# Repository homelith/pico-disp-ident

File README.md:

# pico-disp-ident

## これは何？

- RP2040 搭載ボードと PicoDVI (https://github.com/Wren6991/PicoDVI) を使って、DVI ディスプレイに番号入りのテストパターン表示をさせるツールです。
- PicoDVI の feat/x8scale ブランチ (https://github.com/homelith/PicoDVI/tree/feat/x8scale) 版を用いることで、80x60 画像を VGA 640x480 ディスプレイに引き延ばして表示します。

## ハードウェア構築

- 記載中

## ソフトウェアビルド

- 環境準備
  + Linux ベースの OS 各種上でコンパイル可能と想定 (x86_64 ネイティブの ubuntu 22.04 LTS と WSL2 上の ubuntu 22.04 LTS で試験済)
  + パッケージインストール : `sudo apt install git gcc make cmake gcc-arm-none-eabi libnewlib-arm-none-eabi build-essential golang`

- uf2 バイナリをコンパイルする手順
  + 下記手順でコンパイル後、`sw/build/app/pico-disp-ident.uf2` が得られます

```
$ git clone --recursive git@github.com:homelith/pico-disp-ident.git
$ cd pico-disp-ident/sw
$ make
```

## デバイスを動作させる手順

- Raspberry Pi Pico への uf2 ファイルダウンロード
  + BOOTSEL ボタンを押しながら Raspi Pico の電源を投入することで、USB ポートがマスストレージデバイスとして認識されます
  + `pico-disp-ident.uf2` ファイルを該当ストレージの直下に置くことで書き込みとセルフリセットが行われます

- ボタンを押下すると表示画像と対応する 7seg の表示番号が切り替わります

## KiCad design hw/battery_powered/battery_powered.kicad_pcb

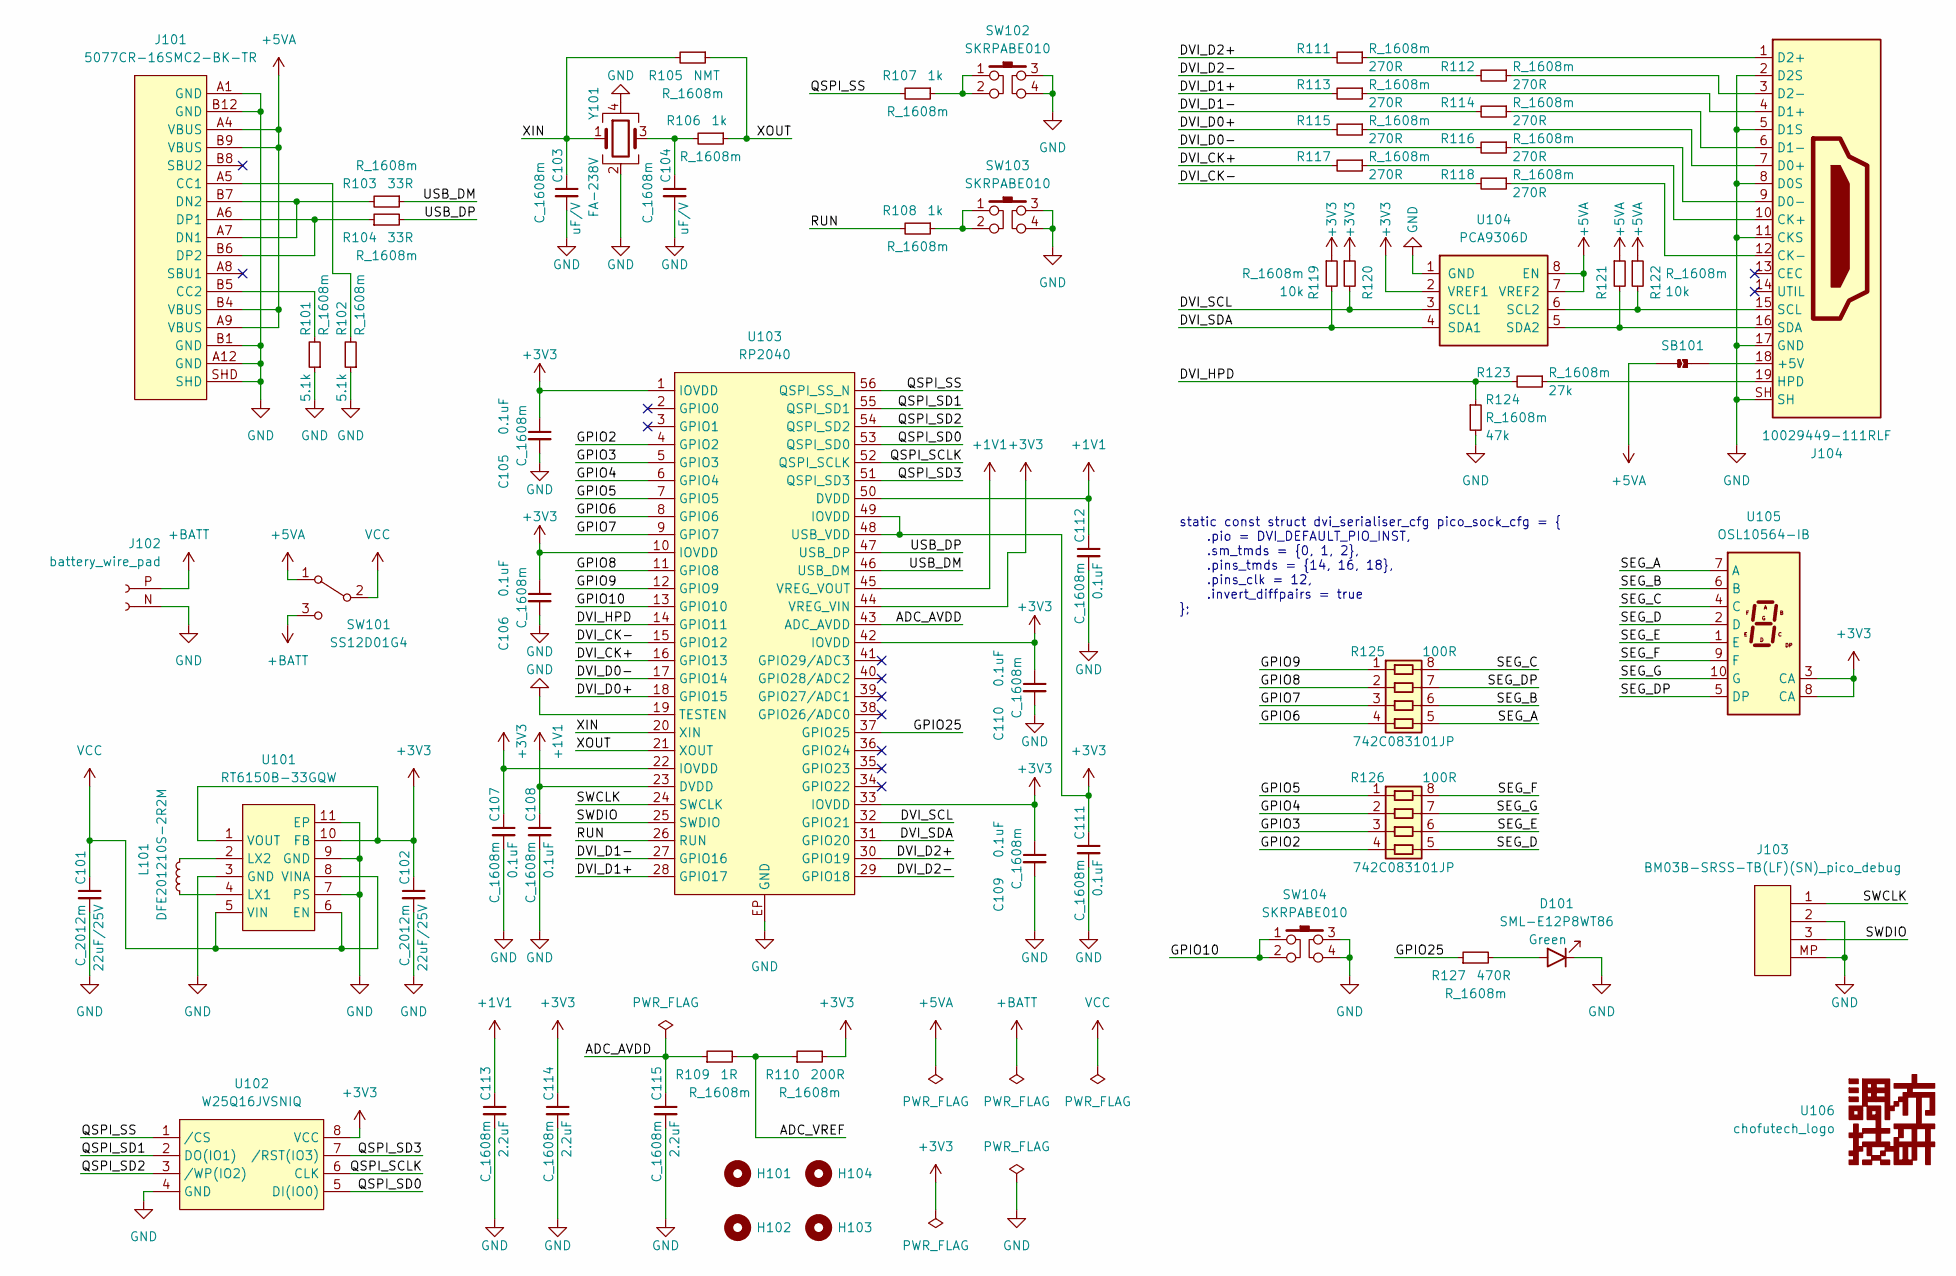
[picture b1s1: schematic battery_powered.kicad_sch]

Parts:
C101, C102: C_2012m
C103, C104, C105, C106, C107, C108, C109, C110, C111, C112, C113, C114, C115: C_1608m
D101: SML-E12P8WT86
H101, H102, H103, H104: MountingHole_2.2mm_M2; MountingHole_3.2mm_M3
J101: 5077CR-16SMC2-BK-TR; 5077CR-16SMC2-BK-TR_hand
J102: battery_wire_pad
J103: BM03B-SRSS-TB(LF)(SN)_pico_debug; BM03B-SRSS-TB(LF)(SN)_hand
J104: 10029449-111RLF; 10029449-111RLF_hand
L101: DFE201210S-2R2M
R101, R102, R103, R104, R105, R106, R107, R108, R109, R110, R111, R112, R113, R114, R115, R116, R117, R118, R119, R120, R121, R122, R123, R124, R127: R_1608m
R125, R126: 742C083101JP
SB101: jumper_2pole_solder
SW101: SS12D01G4
SW102, SW103, SW104: SKRPABE010; SKRPABE010_hand
U101: RT6150B-33GQW
U102: W25Q16JVSNIQ
U103: RP2040
U104: PCA9306D
U105: OSL10564-IB
U106: chofutech_logo; chofutech_logo_6.6mm
Y101: FA-238V

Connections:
+1V1: C108.1, C112.1, C113.1, U103.23 (DVDD), U103.45 (VREG_VOUT), U103.50 (DVDD)
+3V3: C102.1, C105.1, C106.1, C107.1, C109.1, C110.1, C111.1, C114.1, R110.2, R119.1, R120.1, U101.1 (VOUT), U101.10 (FB), U102.8 (VCC), U103.1 (IOVDD), U103.10 (IOVDD), U103.22 (IOVDD), U103.33 (IOVDD), U103.42 (IOVDD), U103.44 (VREG_VIN), U103.48 (USB_VDD), U103.49 (IOVDD), U104.2 (VREF1), U105.3 (CA), U105.8 (CA)
+5VA: J101.A4 (VBUS), J101.A9 (VBUS), J101.B4 (VBUS), J101.B9 (VBUS), R121.1, R122.1, SB101.1 (A), SW101.1 (A), U104.7 (VREF2), U104.8 (EN)
+BATT: J102.P (Pin_1), SW101.3 (C)
/ADC_AVDD: C115.1, R109.1, U103.43 (ADC_AVDD)
/ADC_VREF: R109.2, R110.1
/DVI_CK+: R117.2, U103.16 (GPIO13)
/DVI_CK-: R118.2, U103.15 (GPIO12)
/DVI_D0+: R115.2, U103.18 (GPIO15)
/DVI_D0-: R116.2, U103.17 (GPIO14)
/DVI_D1+: R113.2, U103.28 (GPIO17)
/DVI_D1-: R114.2, U103.27 (GPIO16)
/DVI_D2+: R111.2, U103.30 (GPIO19)
/DVI_D2-: R112.2, U103.29 (GPIO18)
/DVI_HPD: R123.2, R124.1, U103.14 (GPIO11)
/DVI_SCL: R120.2, U103.32 (GPIO21), U104.3 (SCL1)
/DVI_SDA: R119.2, U103.31 (GPIO20), U104.4 (SDA1)
/GPIO2: R126.4, U103.4 (GPIO2)
/GPIO3: R126.3, U103.5 (GPIO3)
/GPIO4: R126.2, U103.6 (GPIO4)
/GPIO5: R126.1, U103.7 (GPIO5)
/GPIO6: R125.4, U103.8 (GPIO6)
/GPIO7: R125.3, U103.9 (GPIO7)
/GPIO8: R125.2, U103.11 (GPIO8)
/GPIO9: R125.1, U103.12 (GPIO9)
/GPIO10: SW104.1, SW104.2, U103.13 (GPIO10)
/GPIO25: R127.1, U103.37 (GPIO25)
/QSPI_SCLK: U102.6 (CLK), U103.52 (QSPI_SCLK)
/QSPI_SD0: U102.5 (DI(IO0)), U103.53 (QSPI_SD0)
/QSPI_SD1: U102.2 (DO(IO1)), U103.55 (QSPI_SD1)
/QSPI_SD2: U102.3 (/WP(IO2)), U103.54 (QSPI_SD2)
/QSPI_SD3: U102.7 (/RST(IO3)), U103.51 (QSPI_SD3)
/QSPI_SS: R107.2, U102.1 (/CS), U103.56 (QSPI_SS_N)
/RUN: R108.2, U103.26 (RUN)
/SEG_A: R125.5, U105.7 (A)
/SEG_B: R125.6, U105.6 (B)
/SEG_C: R125.8, U105.4 (C)
/SEG_D: R126.5, U105.2 (D)
/SEG_DP: R125.7, U105.5 (DP)
/SEG_E: R126.6, U105.1 (E)
/SEG_F: R126.8, U105.9 (F)
/SEG_G: R126.7, U105.10 (G)
/SWCLK: J103.1, U103.24 (SWCLK)
/SWDIO: J103.3, U103.25 (SWDIO)
/USB_DM: R103.1, U103.46 (USB_DM)
/USB_DP: R104.2, U103.47 (USB_DP)
/XIN: C103.1, R105.2, U103.20 (XIN), Y101.1
/XOUT: R105.1, R106.1, U103.21 (XOUT)
GND: C101.2, C102.2, C103.2, C104.2, C105.2, C106.2, C107.2, C108.2, C109.2, C110.2, C111.2, C112.2, C113.2, C114.2, C115.2, D101.1 (K), J101.A1 (GND), J101.A12 (GND), J101.B1 (GND), J101.B12 (GND), J101.SHD, J102.N (Pin_2), J103.2, J103.MP, J104.2 (D2S), J104.5 (D1S), J104.8 (D0S), J104.11 (CKS), J104.17 (GND), J104.SH, R101.1, R102.1, R124.2, SW102.3, SW102.4, SW103.3, SW103.4, SW104.3, SW104.4, U101.3 (GND), U101.7 (PS), U101.9 (GND), U101.11 (EP), U102.4 (GND), U103.19 (TESTEN), U103.EP (GND), U104.1 (GND), Y101.2, Y101.4
unnamed: C104.1, R106.2, Y101.3
unnamed: D101.2 (A), R127.2
unnamed: J101.A5 (CC1), R102.2
unnamed: J101.A6 (DP1), J101.B6 (DP2), R104.1
unnamed: J101.A7 (DN1), J101.B7 (DN2), R103.2
unnamed: J101.B5 (CC2), R101.2
unnamed: J104.1 (D2+), R111.1
unnamed: J104.3 (D2-), R112.1
unnamed: J104.4 (D1+), R113.1
unnamed: J104.6 (D1-), R114.1
unnamed: J104.7 (D0+), R115.1
unnamed: J104.9 (D0-), R116.1
unnamed: J104.10 (CK+), R117.1
unnamed: J104.12 (CK-), R118.1
unnamed: J104.15 (SCL), R122.2, U104.6 (SCL2)
unnamed: J104.16 (SDA), R121.2, U104.5 (SDA2)
unnamed: J104.18 (+5V), SB101.2 (B)
unnamed: J104.19 (HPD), R123.1
unnamed: L101.1, U101.2 (LX2)
unnamed: L101.2, U101.4 (LX1)
unnamed: R107.1, SW102.1, SW102.2
unnamed: R108.1, SW103.1, SW103.2
VCC: C101.1, SW101.2 (B), U101.5 (VIN), U101.6 (EN), U101.8 (VINA)

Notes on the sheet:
static const struct dvi_serialiser_cfg pico_sock_cfg = { .pio = DVI_DEFAULT_PIO_INST, .sm_tmds = {0, 1, 2}, .pins_tmds = {14, 16, 18}, .pins_clk = 12, .invert_diffpairs = true };

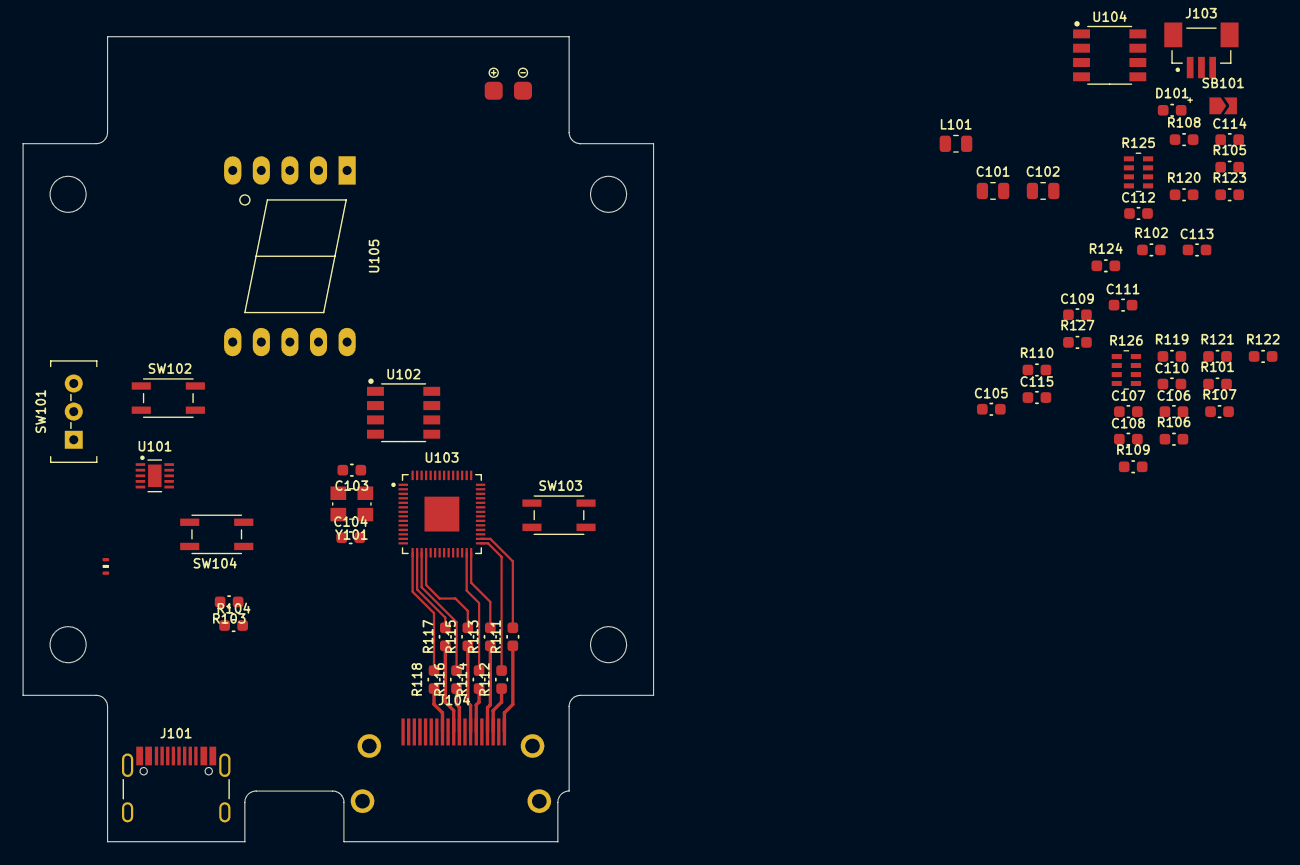
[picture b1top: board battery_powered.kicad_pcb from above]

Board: 4 copper layers, 56.0 x 71.5 mm, 64 parts (0 on the bottom side), 72 nets.

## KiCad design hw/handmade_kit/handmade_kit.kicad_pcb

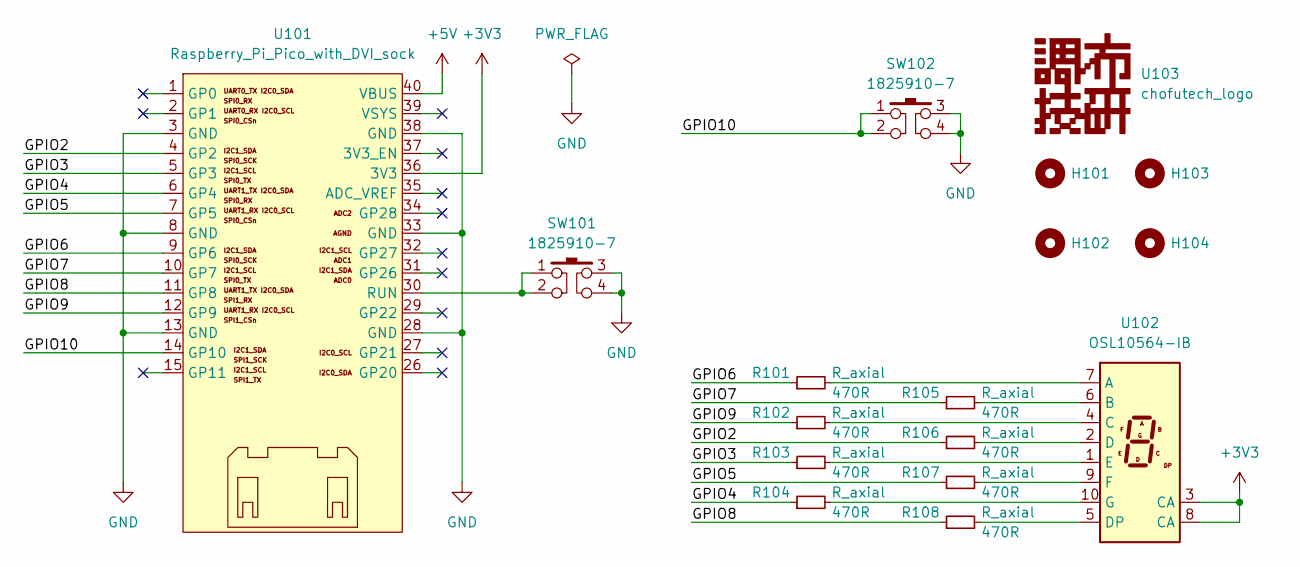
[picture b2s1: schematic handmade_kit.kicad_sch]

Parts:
H101, H102, H103, H104: MountingHole_2.2mm_M2
R101, R102, R103, R104, R105, R106, R107, R108: R_axial
SW101, SW102: 1825910-7
U101: Raspberry_Pi_Pico_with_DVI_sock
U102: OSL10564-IB
U103: chofutech_logo; chofutech_logo_6.6mm

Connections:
+3V3: U101.36 (3V3), U102.3 (CA), U102.8 (CA)
+5V: U101.40 (VBUS)
/GPIO2: R106.1, U101.4 (GP2)
/GPIO3: R103.1, U101.5 (GP3)
/GPIO4: R104.1, U101.6 (GP4)
/GPIO5: R107.1, U101.7 (GP5)
/GPIO6: R101.1, U101.9 (GP6)
/GPIO7: R105.1, U101.10 (GP7)
/GPIO8: R108.1, U101.11 (GP8)
/GPIO9: R102.1, U101.12 (GP9)
/GPIO10: SW102.1, SW102.2, U101.14 (GP10)
GND: SW101.3, SW101.4, SW102.3, SW102.4, U101.3 (GND), U101.8 (GND), U101.13 (GND), U101.28 (GND), U101.33 (GND), U101.38 (GND)
unnamed: R101.2, U102.7 (A)
unnamed: R102.2, U102.4 (C)
unnamed: R103.2, U102.1 (E)
unnamed: R104.2, U102.10 (G)
unnamed: R105.2, U102.6 (B)
unnamed: R106.2, U102.2 (D)
unnamed: R107.2, U102.9 (F)
unnamed: R108.2, U102.5 (DP)
unnamed: SW101.1, SW101.2, U101.30 (RUN)

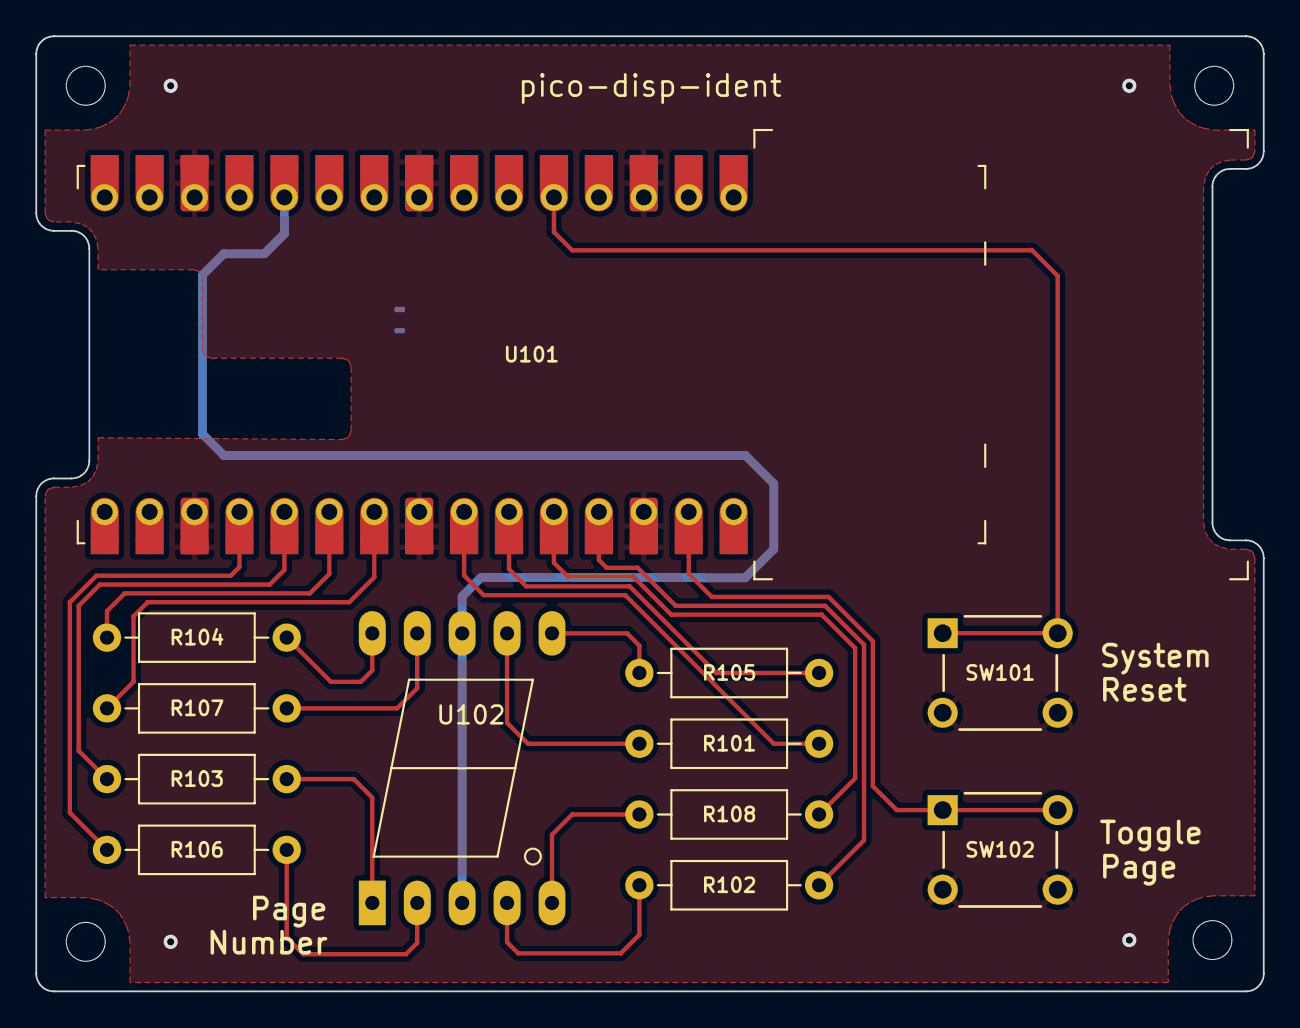
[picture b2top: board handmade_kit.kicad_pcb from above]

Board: 2 copper layers, 69.4 x 54.0 mm, 17 parts (1 on the bottom side), 20 nets.

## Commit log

2024-05-17 add handmade_kit pcb design and battery_powered pcb skelton
2024-05-17 plotted handmade_kit r01
2024-05-17 filled battery_powered schematics
2024-05-18 add battery_powered footprints
2024-05-22 add DVI output circuit to battery_powered composition
2024-05-23 change DVI pin assignment (PicoDVI cfg written in schematic)
2024-05-26 fixed battery_powered artwork and add .gitkeep to build dir
